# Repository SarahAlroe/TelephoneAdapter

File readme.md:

# TelephoneAdapter

Circuits and prints to let you use a landline (presumably carbon microphone) telephone as a microphone.
More info [here](http://sarah.alroe.dk/2022/TelephoneAdapter/).

One directory is for a phantom powered adapter. The other is for one with externally supplied power.

To produce an adapter without modification, print the stl parts from that folder, print and etch the corresponding circut, solder and assemble.
The root directory pdf contains a ready to print and mask set of positives for both circuits.

BOMs with suggested component sources follows:

Phantom Power BOM:

* 1 Generic 1/4W resistor of a couple hundred ohms
* 1 22 µF capacitor (ceramic or similar)
* 1 200 µF capacitor (electrolytic)
* 2 Zener diodes (5.1V or there about)
* 1 600:600 transformer with center tap eg. [42TL016-RC](https://www.aliexpress.com/wholesale?SearchText=42TL016-RC)
* 1 XLR plug eg. [from R connector](https://www.aliexpress.com/item/4000563708302.html)
* 1 Telephone plug eg. [this](https://elektronik-lavpris.dk/p125084/telstik-hun-wh-telefonstik-hun-hvid/), though check your local charity shop first.
* 6 M3x16 bolts
* 4 M3X40 bolts
* 10 M3 Nuts
* All 3D printed parts

External Power BOM:

* 1 Generic 1/4W resistor of a couple hundred ohms
* 1 22 µF capacitor (ceramic or similar)
* 1 200 µF capacitor (electrolytic)
* 2 Zener diodes (5.1V or there about)
* 1 600:600 isolation transformer eg. [EI14](https://www.aliexpress.com/wholesale?SearchText=EI14)
* 1 Telephone plug eg. [this](https://elektronik-lavpris.dk/p125084/telstik-hun-wh-telefonstik-hun-hvid/), though check your local charity shop first.
* 4 M3x16 bolts
* 4 M3X40 bolts
* 8 M3 Nuts
* All 3D printed parts

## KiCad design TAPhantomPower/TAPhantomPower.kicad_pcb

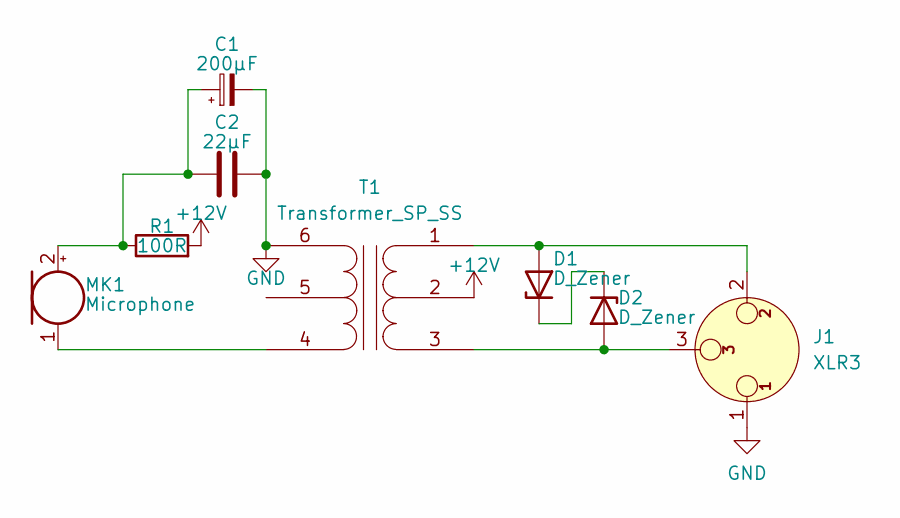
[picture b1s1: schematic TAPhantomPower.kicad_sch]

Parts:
C1: 200µF; CP_Radial_D8.0mm_P5.00mm
C2: 22µF; C_Disc_D4.7mm_W2.5mm_P5.00mm
D1, D2: D_Zener; D_DO-35_SOD27_P7.62mm_Horizontal
J1: XLR3; PinHeader_1x03_P2.54mm_Vertical
MK1: Microphone; PinHeader_1x02_P2.54mm_Vertical
R1: 100R; R_Axial_DIN0207_L6.3mm_D2.5mm_P7.62mm_Horizontal
T1: Transformer_SP_SS; Transformer_42TL

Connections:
+12V: R1.2, T1.2 (AC)
GND: C1.2, C2.2, J1.1, T1.6 (SB)
unnamed: C1.1, C2.1, MK1.2 (+), R1.1
unnamed: D1.1 (K), D2.1 (K)
unnamed: D1.2 (A), J1.2, T1.1 (AA)
unnamed: D2.2 (A), J1.3, T1.3 (AB)
unnamed: MK1.1 (-), T1.4 (SA)

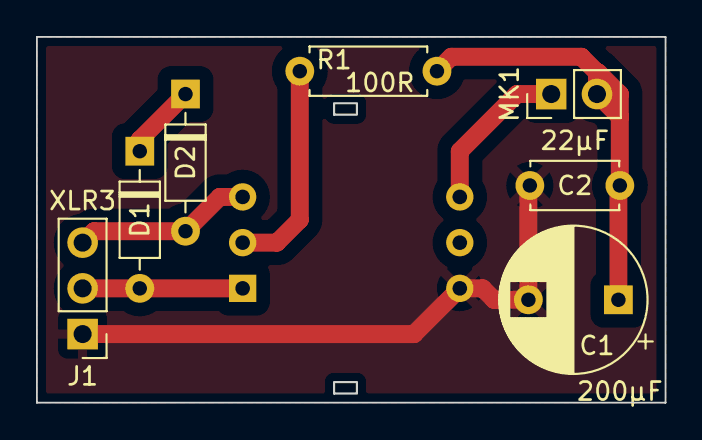
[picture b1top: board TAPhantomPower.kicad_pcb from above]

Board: 2 copper layers, 34.9 x 20.3 mm, 8 parts (1 on the bottom side), 7 nets.

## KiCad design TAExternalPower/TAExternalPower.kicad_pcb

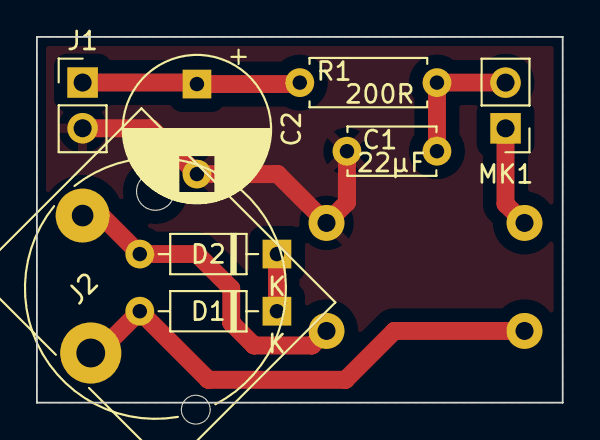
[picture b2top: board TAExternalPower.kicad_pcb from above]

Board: 2 copper layers, 29.2 x 20.3 mm, 9 parts (1 on the bottom side), 7 nets.

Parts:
C1: 22µF; C_Disc_D4.7mm_W2.5mm_P5.00mm
C2: 200µF; CP_Radial_D8.0mm_P5.00mm
D1, D2: D_Zener; D_DO-35_SOD27_P7.62mm_Horizontal
J1: Barrel_Jack; PinHeader_1x02_P2.54mm_Vertical
J2: AudioJack2_Ground; Jack_6.35mm_Neutrik_NJ2FD-V_Vertical
MK1: Microphone; PinHeader_1x02_P2.54mm_Vertical
R1: 200R; R_Axial_DIN0207_L6.3mm_D2.5mm_P7.62mm_Horizontal
T1: Transformer_1P_1S; Transformer_Toroid_Horizontal_D9.0mm_Amidon-T30

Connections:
+12V: C2.1, J1.1, R1.2
GND: C1.2, C2.2, J1.2, T1.1 (AA)
unnamed: C1.1, MK1.2 (+), R1.1
unnamed: D1.1 (K), D2.1 (K)
unnamed: D1.2 (A), J2.S, T1.4 (SB)
unnamed: D2.2 (A), J2.T, T1.3 (SA)
unnamed: MK1.1 (-), T1.2 (AB)

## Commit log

2022-07-23 Init
